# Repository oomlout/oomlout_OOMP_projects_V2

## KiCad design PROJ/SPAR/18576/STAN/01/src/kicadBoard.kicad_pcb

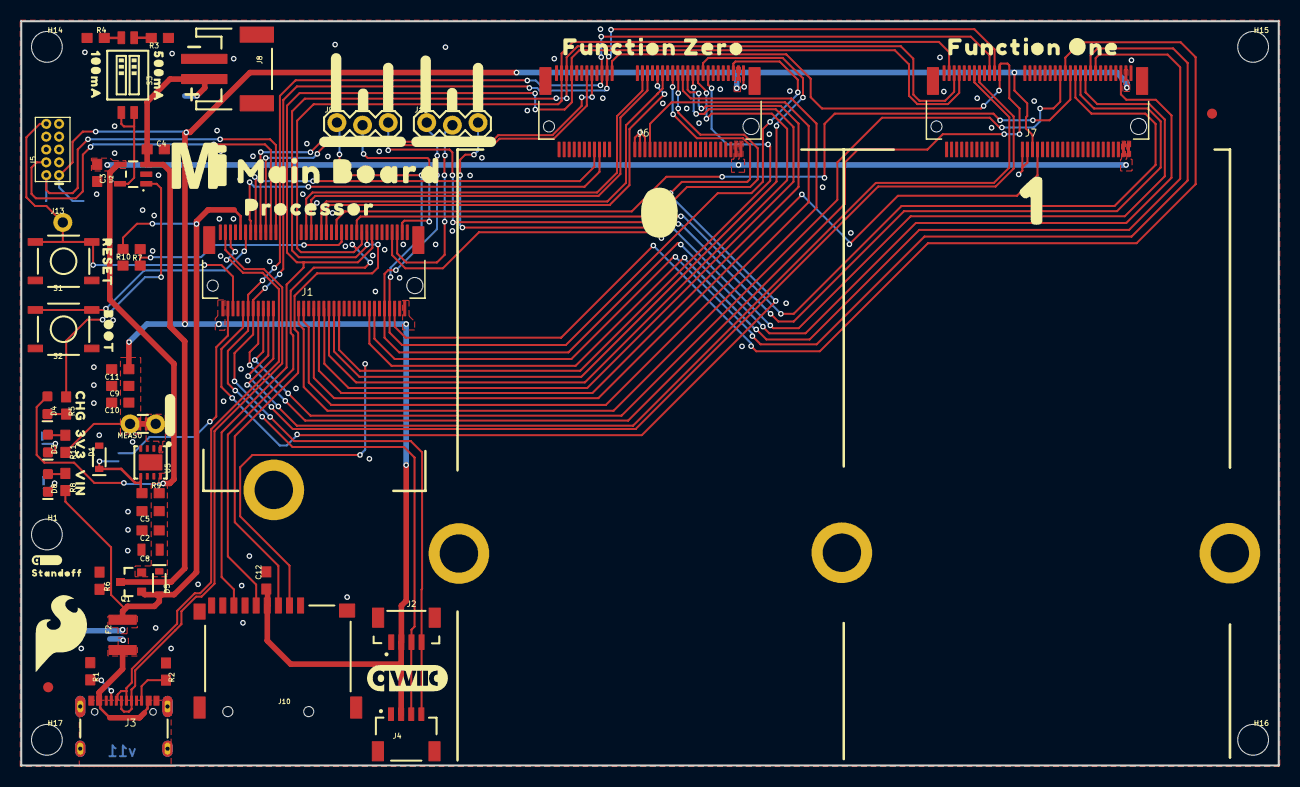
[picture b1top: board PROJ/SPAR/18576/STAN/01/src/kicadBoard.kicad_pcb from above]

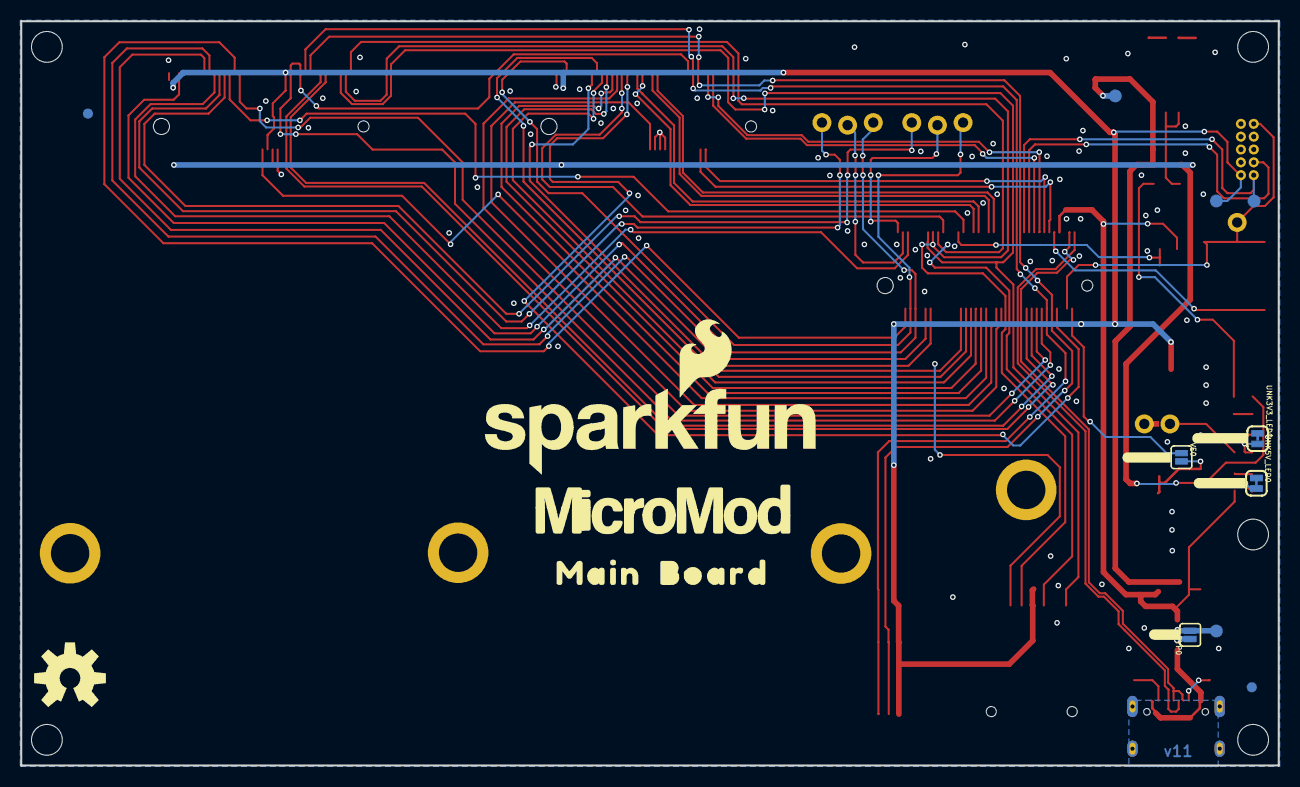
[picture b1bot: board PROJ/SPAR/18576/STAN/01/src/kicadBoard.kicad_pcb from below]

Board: 2 copper layers, 124.5 x 73.7 mm, 104 parts (19 on the bottom side), 65 nets.

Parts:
BYP0: JUMPER-SMT_2_NO_SILK; SMT-JUMPER_2_NO_SILK
C2, C11: 0.22uF; 0603
C3, C4: 4.7uF; 0603
C5, C10, C12: 0.1uF; 0603
C8: 10uF; 0805
C9: 1.0uF; 0603
D1: 3.3V; SOD-323
D3, D8: RED; LED-0603
D4: Yellow; LED-0603
D5: 1A/23V/620mV; SOD-323
F2: 6V/2A; 1210
FD1, FD2, FD3, FD4: FIDUCIAL1X2; FIDUCIAL-1X2
FRAME1: FRAME-LEDGER; CREATIVE_COMMONS
FRAME2: FRAME-LEDGERNO_FOOTPRINT; DUMMY
H1, H14, H15, H16, H17: STAND-OFFTIGHT; STAND-OFF-TIGHT
H2, H3, H4, H8: STAND-OFF-REFLOW-M2.5_2.5MM_TALL; STAND-OFF-REFLOW-M2.5
J1: MICROMOD-2222-C; M.2-CONNECTOR-E
J2: Vertical Qwiic Connector; JST04_1MM_VERT
J3: USB-C-16P-2LAYER-PADS
J4: QWIIC_RIGHT_ANGLE; JST04_1MM_RA
J5: CORTEX_JTAG_DEBUG_MINIMUM_PTH; 2X5-PTH-1.27MM
J6, J7: MICROMOD_FUNCTION_MAIN; M.2-CONNECTOR-E-FUNCTION-STANDARD
J8: JST-2-SMD
J9, J11: 1X03_LOCK
J10: MICRO-SD-PUSH-PUSH-EXT-PIN; MICROSD-EXTERNALPIN
J13: 1X01_NO_SILK
LOGO1: QWIIC_LOGO_8MM; QWIIC_8MM
LOGO2: SFE_LOGO_NAME_FLAME.3_INCH; SFE_LOGO_NAME_FLAME_.3
LOGO3: OSHW-LOGOL; OSHW-LOGO-L
MEAS0: JUMPER-COMBO_2_NC_TRACE; COMBO-JUMPER_2_NC_TRACE
Q1: 3.1A/30V/105mΩ; SOT23-3
R1, R2: 5.1k; 0603
R3: 2.0k; 0603
R4, R6, R7: 10k; 0603
R5, R11: 1k; 0603
R8: 4.7k; 0603
R9: 100k; 0603
R10: 20k; 0603
S1: Reset; TACTILE_SWITCH_SMD_5.2MM
S2: BOOT; TACTILE_SWITCH_SMD_5.2MM
S3: DIP-02-SMD-50MIL; DIPSWITCH-02-50MIL
TP1, TP2, TP3, TP4: TEST-POINT3X5; PAD.03X.05
U2: MCP73831; SOT23-5
U5: AP7361C-33; UDFN-8
U$1: #3V3_EN#18
U$2: #3V3_LED#17
U$3: #VIN_LED#16
U$4: 3V332533
U$5: VIN32532
U$6: CHG32531
U$7: #PTC#18
U$8: BOOT32541
U$9: RESET32540
U$10: PROCESSOR525
U$11: FUNCTION_ZERO520
U$12: FUNCTION_ONE524
U$13: MAIN523
U$14: MICROMOD_MI_LOGO_1
U$15: 0523
U$16: 1524
U$17: MICROMOD_LOGO_1
U$18: BOARD524
U$19: 100MA6
U$20: 500MA101
U$21: MAIN_BOARD5523
U$22: QWIIC_3MM
U$23: STANDOFF501
U$24: SFE_LOGO_FLAME_.3
U$25: #ALT_PWR_EN0#510
U$26: #ALT_PWR_EN1#510
U$27: #FC1#G3#518
U$28: #FC1#G4#518
U$29: #G6#517
U$30: #PWR_EN0#517
U$31: #PWR_EN1#517
U$32: #G5#517
U$33: #MEAS#40313513
UNK3V3_LED0, UNK5V_LED0: JUMPER-SMT_2_NC_TRACE_SILK; SMT-JUMPER_2_NC_TRACE_SILK
VE0: JUMPER-SMT_2_NO_SILK; SMT-JUMPER_2_NO_SILK

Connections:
3.3V: C9.1, C10.1, C11.1, C12.1, J1.2, J1.74, J2.2, J4.2, J5.1, J6.73, J7.36, J7.73, J10.4, MEAS0.2, MEAS0.4, R11.2, TP2.1
3.3V_EN: J1.4, VE0.1
3.3V_EN_VE: D1.C, R9.1, U5.5, VE0.2
A0-PROCESSOR: J1.34, J6.38
A1-PROCESSOR: J1.38, J7.38
CTS1-PROCESSOR: J1.15, J6.16
D0-PROCESSOR: J1.10, J6.47
D1-PROCESSOR: J1.18, J7.47
D+: J1.3, J3.A6, J3.B6
D-: J1.5, J3.A7, J3.B7
G0-PROCESSOR: J1.40, J6.53
G1-PROCESSOR: J1.42, J6.55
G2-PROCESSOR: J1.44, J6.57
G3-PROCESSOR: J1.46, J6.59
G4-PROCESSOR/SD_CARD_~CS: J1.48, J6.61, J10.2
G5-JUMPER: J1.71, J11.2
G5-PROCESSOR: J7.53, J9.3
G6-PROCESSOR: J7.55, J11.3
G7-PROCESSOR: J1.69, J7.57
G8-PROCESSOR: J1.62, J7.59
G9-PROCESSOR: J1.60, J7.61
GND: C2.2, C3.2, C4.2, C5.2, C8.2, C9.2, C10.2, C11.2, C12.2, D1.A, H2.1, H3.1, H4.1, H8.1, J1.1, J1.7, J1.33, J1.36, J1.39, J1.45, J1.75, J2.1, J3.GND, J3.GND2, J4.1, J5.3, J5.5, J5.9, J6.1, J6.32, J6.33, J6.34, J6.36, J6.39, J6.45, J6.75, J7.1, J7.32, J7.33, J7.34, J7.39, J7.45, J7.75, J8.1, J10.6, J10.10, J10.11, J10.12, J10.13, R1.1, R2.1, R3.1, R4.1, R6.1, R7.1, S1.1, S1.2, S2.1, S2.2, U2.2, U5.4, U5.EP, UNK3V3_LED0.1, UNK5V_LED0.1
HOST_D+: J1.35, J6.35
HOST_D-: J1.37, J6.37
I2C_SCL: J1.14, J2.4, J4.4, J6.21, J7.21
I2C_SDA: J1.12, J2.3, J4.3, J6.19, J7.19
I2C_~INT: J1.16, J6.23, J7.23
unnamed: MEAS0.1, MEAS0.3, U5.1
unnamed: D8.C, UNK5V_LED0.2
unnamed: D3.A, R11.1
unnamed: J3.B5, R2.2
unnamed: J3.A5, R1.2
unnamed: R3.2, S3.1
unnamed: BYP0.1, F2.1, J3.VBUS1, J3.VBUS2
unnamed: R4.2, S3.2
unnamed: J1.73, J9.2
unnamed: D3.C, UNK3V3_LED0.2
unnamed: D8.A, R8.1
unnamed: D4.C, R5.2
unnamed: R5.1, U2.1
PROCESSOR_CAN-RX: J1.41, J6.43
PROCESSOR_CAN-TX: J1.43, J6.41
PWM0-PROCESSOR: J1.32, J6.51
PWM1-PROCESSOR: J1.47, J7.51
PWR_EN0: J1.68, J6.71, J9.1
PWR_EN1: J1.66, J7.71, J11.1
RTS1-PROCESSOR: J1.13, J6.18
RX1-PROCESSOR: J1.19, J6.13
RX2-PROCESSOR: J1.20, J7.13
SHLD: S3.3, S3.4, U2.5
SPI_PROCESSOR_SCK: J1.57, J6.3, J7.3, J10.5
SPI_PROCESSOR_SDI: J1.61, J6.7, J7.7, J10.7
SPI_PROCESSOR_SDO: J1.59, J6.5, J7.5, J10.3
SWDCK: J1.21, J5.4
SWDIO: J1.23, J5.2, TP1.1
TX1-PROCESSOR: J1.17, J6.15
TX2-PROCESSOR: J1.22, J7.15
VCC: C2.1, C3.1, C5.1, C8.1, D4.A, D5.C, J6.72, J6.74, J7.72, J7.74, Q1.2, R9.2, U2.4, U5.8
VIN: BYP0.2, D5.A, F2.2, J1.9, Q1.1, R6.2, R8.2, R10.2, TP4.1
VIN/3: J1.49, R7.2, R10.1
V_BATT: C4.1, J8.2, Q1.3, TP3.1, U2.3
~BOOT: J1.11, S2.3, S2.4
~CS0-PROCESSOR: J1.55, J6.49
~CS1-PROCESSOR: J1.70, J7.49
~RESET: J1.6, J5.10, J13.1, S1.3, S1.4

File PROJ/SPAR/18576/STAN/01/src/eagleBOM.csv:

"Part";"Value";"Device";"Package";"Description";"DESIGNER";"PROD_ID";"REV";"SF_ID";"VALUE";
"3V3_LED";"JUMPER-SMT_2_NC_TRACE_SILK";"JUMPER-SMT_2_NC_TRACE_SILK";"SMT-JUMPER_2_NC_TRACE_SILK";"Normally closed trace jumper";"";"";"";"";"";
"5V_LED";"JUMPER-SMT_2_NC_TRACE_SILK";"JUMPER-SMT_2_NC_TRACE_SILK";"SMT-JUMPER_2_NC_TRACE_SILK";"Normally closed trace jumper";"";"";"";"";"";
"BYP";"JUMPER-SMT_2_NO_SILK";"JUMPER-SMT_2_NO_SILK";"SMT-JUMPER_2_NO_SILK";"Normally open jumper";"";"";"";"";"";
"C2";"0.22uF";"0.22UF-0603-25V-10%";"0603";"0.22µF ceramic capacitors";"";"CAP-07822";"";"";"0.22uF";
"C3";"4.7uF";"4.7UF-0603-6.3V-(10%)";"0603";"4.7µF ceramic capacitors";"";"CAP-08280";"";"";"4.7uF";
"C4";"4.7uF";"4.7UF-0603-35V-(20%)";"0603";"4.7µF ceramic capacitors";"";"CAP-14106";"";"";"4.7uF";
"C5";"0.1uF";"0.1UF-0603-25V-(+80/-20%)";"0603";"0.1µF ceramic capacitors";"";"CAP-00810";"";"";"0.1uF";
"C8";"10uF";"10UF-0805-10V-10%";"0805";"10.0µF ceramic capacitors";"";"CAP-11330";"";"";"10uF";
"C9";"1.0uF";"1.0UF-0603-16V-10%";"0603";"1µF ceramic capacitors";"";"CAP-00868";"";"";"1.0uF";
"C10";"0.1uF";"0.1UF-0603-25V-(+80/-20%)";"0603";"0.1µF ceramic capacitors";"";"CAP-00810";"";"";"0.1uF";
"C11";"0.22uF";"0.22UF-0603-25V-10%";"0603";"0.22µF ceramic capacitors";"";"CAP-07822";"";"";"0.22uF";
"C12";"0.1uF";"0.1UF-0603-25V-(+80/-20%)";"0603";"0.1µF ceramic capacitors";"";"CAP-00810";"";"";"0.1uF";
"D1";"3.3V";"DIODE-ZENER-MM3Z3V3T1G";"SOD-323";"Zener Diode";"";"DIO-11284";"";"";"3.3V";
"D3";"RED";"LED-RED0603";"LED-0603";"Red SMD LED";"";"DIO-00819";"";"";"RED";
"D4";"Yellow";"LED-YELLOW0603";"LED-0603";"Yellow SMD LED";"";"DIO-09003";"";"";"Yellow";
"D5";"1A/23V/620mV";"DIODE-SCHOTTKY-BAT20J";"SOD-323";"Schottky diode";"";"DIO-11623";"";"";"1A/23V/620mV";
"D8";"RED";"LED-RED0603";"LED-0603";"Red SMD LED";"";"DIO-00819";"";"";"RED";
"F2";"6V/2A";"PPTC_6V2A";"1210";"Resettable Fuse PPTC";"";"RES-14313";"";"";"6V/2A";
"FD1";"FIDUCIAL1X2";"FIDUCIAL1X2";"FIDUCIAL-1X2";"Fiducial Alignment Points";"";"";"";"";"";
"FD2";"FIDUCIAL1X2";"FIDUCIAL1X2";"FIDUCIAL-1X2";"Fiducial Alignment Points";"";"";"";"";"";
"FD3";"FIDUCIAL1X2";"FIDUCIAL1X2";"FIDUCIAL-1X2";"Fiducial Alignment Points";"";"";"";"";"";
"FD4";"FIDUCIAL1X2";"FIDUCIAL1X2";"FIDUCIAL-1X2";"Fiducial Alignment Points";"";"";"";"";"";
"FRAME1";"FRAME-LEDGER";"FRAME-LEDGER";"CREATIVE_COMMONS";"Schematic Frame - Ledger";"";"";"";"";"";
"H2";"STAND-OFF-REFLOW-M2.5_2.5MM_TALL";"STAND-OFF-REFLOW-M2.5_2.5MM_TALL";"STAND-OFF-REFLOW-M2.5";"Stand Off Reflow Compatible";"";"HW-14899";"";"";"";
"H3";"STAND-OFF-REFLOW-M2.5_2.5MM_TALL";"STAND-OFF-REFLOW-M2.5_2.5MM_TALL";"STAND-OFF-REFLOW-M2.5";"Stand Off Reflow Compatible";"";"HW-14899";"";"";"";
"H4";"STAND-OFF-REFLOW-M2.5_2.5MM_TALL";"STAND-OFF-REFLOW-M2.5_2.5MM_TALL";"STAND-OFF-REFLOW-M2.5";"Stand Off Reflow Compatible";"";"HW-14899";"";"";"";
"H8";"STAND-OFF-REFLOW-M2.5_2.5MM_TALL";"STAND-OFF-REFLOW-M2.5_2.5MM_TALL";"STAND-OFF-REFLOW-M2.5";"Stand Off Reflow Compatible";"";"HW-14899";"";"";"";
"H14";"STAND-OFFTIGHT";"STAND-OFFTIGHT";"STAND-OFF-TIGHT";"Stand Off";"";"";"";"";"";
"H15";"STAND-OFFTIGHT";"STAND-OFFTIGHT";"STAND-OFF-TIGHT";"Stand Off";"";"";"";"";"";
"H16";"STAND-OFFTIGHT";"STAND-OFFTIGHT";"STAND-OFF-TIGHT";"Stand Off";"";"";"";"";"";
"H17";"STAND-OFFTIGHT";"STAND-OFFTIGHT";"STAND-OFF-TIGHT";"Stand Off";"";"";"";"";"";
"J1";"MICROMOD-2222-C";"MICROMOD-2222-C";"M.2-CONNECTOR-E";"MicroMod Connector";"";"CONN-14877";"";"";"";
"J2";"Vertical Qwiic Connector";"QWIIC_CONNECTOR";"JST04_1MM_VERT";"SparkFun I2C Standard Qwiic Connector";"";"CONN-14483";"";"";"Vertical Qwiic Connector";
"J3";"";"USB_C_2-LAYER_PADS";"USB-C-16P-2LAYER-PADS";"USB Type C 16Pin Connector";"";"CONN-14122";"";"";"";
"J4";"QWIIC_RIGHT_ANGLE";"QWIIC_CONNECTORJS-1MM";"JST04_1MM_RA";"SparkFun I2C Standard Qwiic Connector";"";"CONN-13694";"";"";"QWIIC_RIGHT_ANGLE";
"J5";"CORTEX_JTAG_DEBUG_MINIMUM_PTH";"CORTEX_JTAG_DEBUG_MINIMUM_PTH";"2X5-PTH-1.27MM";"Cortex Debug Connector - 10 pin";"";"";"";"";"";
"J6";"MICROMOD_FUNCTION_MAIN";"MICROMOD_FUNCTION_MAIN";"M.2-CONNECTOR-E-FUNCTION-STANDARD";"MicroMod Connector";"";"CONN-14877";"";"";"";
"J7";"MICROMOD_FUNCTION_MAIN";"MICROMOD_FUNCTION_MAIN";"M.2-CONNECTOR-E-FUNCTION-STANDARD";"MicroMod Connector";"";"CONN-14877";"";"";"";
"J8";"";"JST_2MM_MALE";"JST-2-SMD";"JST 2MM MALE RA CONNECTOR";"";"CONN-11443";"";"PRT-08612";"";
"J9";"";"CONN_03LOCK";"1X03_LOCK";"Multi connection point. Often used as Generic Header-pin footprint for 0.1 inch spaced/style header connections";"";"";"";"";"";
"J10";"MICRO-SD-PUSH-PUSH-EXT-PIN";"MICRO-SD-PUSH-PUSH-EXT-PIN";"MICROSD-EXTERNALPIN";"microSD Socket for Transflash";"";"CONN-16110";"";"";"";
"J11";"";"CONN_03LOCK";"1X03_LOCK";"Multi connection point. Often used as Generic Header-pin footprint for 0.1 inch spaced/style header connections";"";"";"";"";"";
"J13";"";"CONN_01PTH_NO_SILK_YES_STOP";"1X01_NO_SILK";"Single connection point. Often used as Generic Header-pin footprint for 0.1 inch spaced/style header connections";"";"";"";"";"";
"LOGO1";"QWIIC_LOGO_8MM";"QWIIC_LOGO_8MM";"QWIIC_8MM";"Qwiic Logos for placement on schematic and PCB. The 5.5mm silk logo is best for placing next to Qwiic connector.";"";"";"";"";"";
"LOGO2";"SFE_LOGO_NAME_FLAME.3_INCH";"SFE_LOGO_NAME_FLAME.3_INCH";"SFE_LOGO_NAME_FLAME_.3";"SparkFun Font Logo w/ Flame";"";"";"";"";"";
"LOGO3";"OSHW-LOGOL";"OSHW-LOGOL";"OSHW-LOGO-L";"Open-Source Hardware (OSHW) Logo";"";"";"";"";"";
"MEAS";"JUMPER-COMBO_2_NC_TRACE";"JUMPER-COMBO_2_NC_TRACE";"COMBO-JUMPER_2_NC_TRACE";"";"";"";"";"";"";
"Q1";"3.1A/30V/105mΩ";"MOSFET_PCH-DMG2307L";"SOT23-3";"P-channel MOSFETs";"";"TRANS-11308";"";"";"3.1A/30V/105mΩ";
"R1";"5.1k";"5.1KOHM5.1KOHM-0603-1/10W-1%";"0603";"";"";"RES-12083";"";"";"5.1k";
"R2";"5.1k";"5.1KOHM5.1KOHM-0603-1/10W-1%";"0603";"";"";"RES-12083";"";"";"5.1k";
"R3";"2.0k";"2.0KOHM-0603-1/10W-5%";"0603";"2kΩ resistor";"";"RES-08296";"";"";"2.0k";
"R4";"10k";"10KOHM-0603-1/10W-1%";"0603";"10kΩ resistor";"";"RES-00824";"";"";"10k";
"R5";"1k";"1KOHM-0603-1/10W-1%";"0603";"1kΩ resistor";"";"RES-07856";"";"";"1k";
"R6";"10k";"10KOHM-0603-1/10W-1%";"0603";"10kΩ resistor";"";"RES-00824";"";"";"10k";
"R7";"10k";"10KOHM-0603-1/10W-1%";"0603";"10kΩ resistor";"";"RES-00824";"";"";"10k";
"R8";"4.7k";"4.7KOHM-0603-1/10W-1%";"0603";"4.7kΩ resistor";"";"RES-07857";"";"";"4.7k";
"R9";"100k";"100KOHM-0603-1/10W-1%";"0603";"100kΩ resistor";"";"RES-07828";"";"";"100k";
"R10";"20k";"20KOHM-0603-1/10W-1%";"0603";"20kΩ resistor";"";"RES-09383";"";"";"20k";
"R11";"1k";"1KOHM-0603-1/10W-1%";"0603";"1kΩ resistor";"";"RES-07856";"";"";"1k";
"S1";"Reset";"MOMENTARY-SWITCH-SPST-SMD-5.2-TALL-REDUNDANT";"TACTILE_SWITCH_SMD_5.2MM";"Momentary Switch (Pushbutton) - SPST";"";"SWCH-14139";"";"";"";
"S2";"BOOT";"MOMENTARY-SWITCH-SPST-SMD-5.2-TALL-REDUNDANT";"TACTILE_SWITCH_SMD_5.2MM";"Momentary Switch (Pushbutton) - SPST";"";"SWCH-14139";"";"";"";
"S3";"DIP-02-SMD-50MIL";"DIP-02-SMD-50MIL";"DIPSWITCH-02-50MIL";"2-Position DIP Switch";"";"SWCH-13215";"";"";"";
"TP1";"TEST-POINT3X5";"TEST-POINT3X5";"PAD.03X.05";"SparkFun Test Points";"";"";"";"";"";
"TP2";"TEST-POINT3X5";"TEST-POINT3X5";"PAD.03X.05";"SparkFun Test Points";"";"";"";"";"";
"TP3";"TEST-POINT3X5";"TEST-POINT3X5";"PAD.03X.05";"SparkFun Test Points";"";"";"";"";"";
"TP4";"TEST-POINT3X5";"TEST-POINT3X5";"PAD.03X.05";"SparkFun Test Points";"";"";"";"";"";
"U2";"MCP73831";"MCP73831";"SOT23-5";"MCP73831T Li-Ion, Li-Pol Controller";"";"IC-09995";"";"";"";
"U5";"AP7361C-33";"AP7361C-33FGEUDFN-8";"UDFN-8";"AP7361C 3.3V LDO Regulator";"";"VREG-14094";"";"";"";
"VE";"JUMPER-SMT_2_NO_SILK";"JUMPER-SMT_2_NO_SILK";"SMT-JUMPER_2_NO_SILK";"Normally open jumper";"";"";"";"";"";

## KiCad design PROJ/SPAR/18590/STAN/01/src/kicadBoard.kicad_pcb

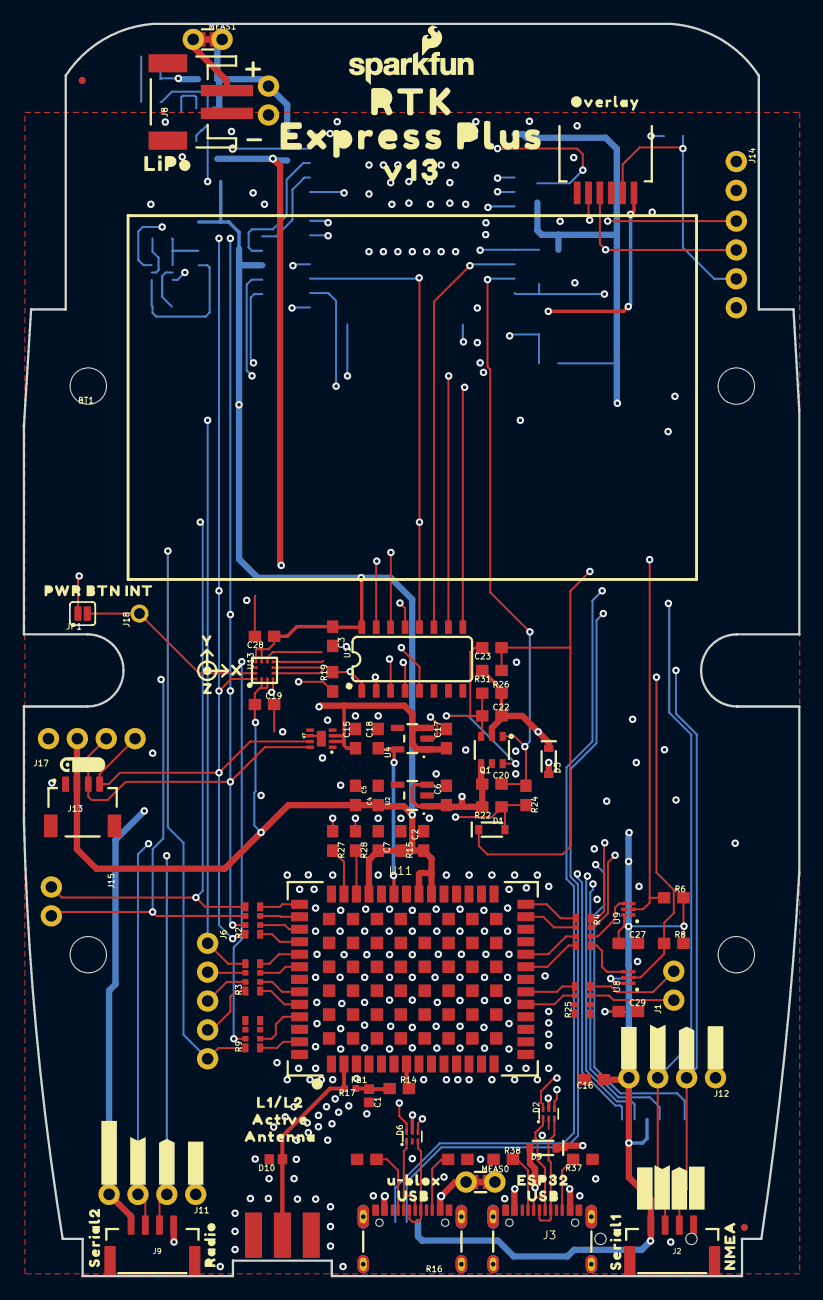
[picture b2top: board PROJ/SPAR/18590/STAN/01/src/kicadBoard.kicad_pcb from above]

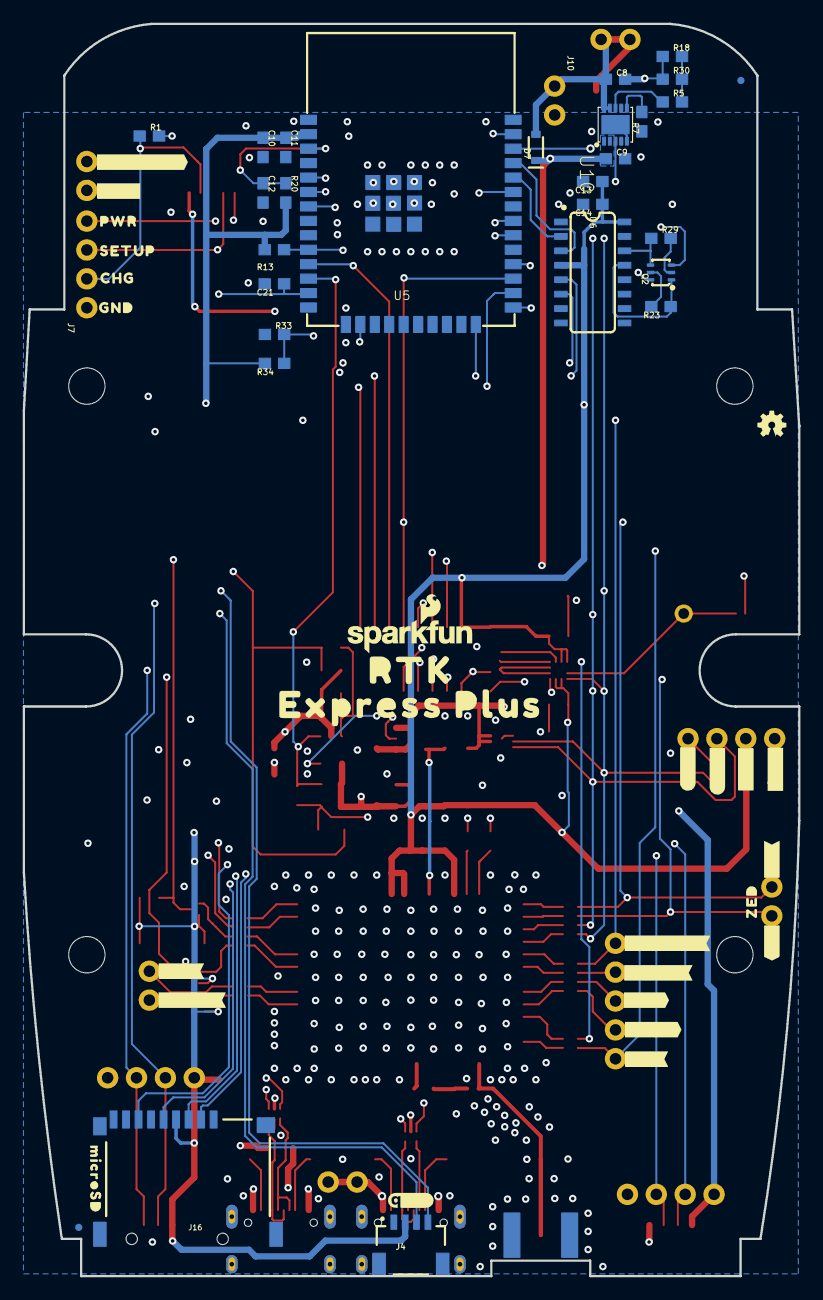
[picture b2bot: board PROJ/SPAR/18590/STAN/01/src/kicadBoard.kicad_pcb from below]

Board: 4 copper layers, 68.2 x 110.1 mm, 171 parts (56 on the bottom side), 92 nets.

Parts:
BT1: LIPO-OUTLINE1000; LIPO-1000
C1: 47pF; 0402
C2, C4, C6, C17, C18: 1.0uF; 0603
C3, C5, C7, C11, C12, C13, C15, C16, C21, C22, C23, C27, C28, C29: 0.1uF; 0603
C8, C9: 4.7uF; 0603
C10, C14, C19, C20: 10uF; 0603
D1: 250mA/100V; SOD-323
D2, D6: PRTR5V0U2F; SOT886
D3, D7, D9: 3A/10V/280mV; SOD-323
D10: PESD0402-0402; 0402
E1: SMA; SMA-EDGE
FB1: 2.66Ω; 0402-TIGHT
FRAME2: FRAME-LEDGER; CREATIVE_COMMONS
FRAME3: FRAME-LEDGERNO_FOOTPRINT; DUMMY
J1, J10, J14, J15: 1X02_NO_SILK
J2, J9: JST-4-SMD-1.25MM-LOCKING
J3, J5: USB Female Type C Connector; USB-C-16P_4LAYER-PADS
J4: Qwiic Right Angle; JST04_1MM_RA
J6: 1X05_NO_SILK
J7, J11, J12: 1X04_NO_SILK
J8: JST-2-SMD
J13: Internal; JST04_1MM_RA
J16: MICRO-SD-PUSH-PUSH-EXT-PIN; MICROSD-EXTERNALPIN
J17: Qwiic Right Angle; 1X04_NO_SILK
J18: 1X01_NO_SILK
J19: FPC_6_1MM-LIF
JP1: JUMPER-SMT_2_NO_SILK; SMT-JUMPER_2_NO_SILK
JP21, JP61, JP71, JP81: FIDUCIALUFIDUCIAL; FIDUCIAL-MICRO
LOGO1: OSHW-LOGOMINI; OSHW-LOGO-MINI
LOGO2, LOGO3: SFE_LOGO_NAME_FLAME.1_INCH; SFE_LOGO_NAME_FLAME_.1
MEAS0, MEAS1: JUMPER-COMBO_2_NC_TRACE; COMBO-JUMPER_2_NC_TRACE
Q1: SIL2308-TP; SOT26
Q2: MBT3904DW1T1; SC70-6
R1: 470; 0603
R2, R3, R4, R9, R25: 33; 1206_RA
R5: 0; 0603
R6, R8, R18, R23, R29, R31, R33: 10k; 0603
R7, R19: 1k; 0603
R13, R15, R20, R22, R26: 100k; 0603
R14: 10; 0603
R16, R17, R37, R38: 5.1k; 0603
R24: 300k; 0603
R27, R28: 27; 0603
R30: 150k; 0603
R34: 3.3k; 0603
U1: 74HC4052D; SO16
U2: AP2112K-3.3; SOT23-5
U4: STLQ015-3.3V; SOT23-5
U5: ESP-WROOM-3232D; ESP-WROOM-32D
U6: CH340C; SO016
U7: MAX17048; DFN-8
U8, U9: NC7SZ14-D; SIP6
U10: MCP73833; DFN-10
U11: U-BLOX_ZED_F9R; UBLOX_ZED_F9R
U13: LIS2DH12; LGA-12-LISDH12
U$1: V130
U$2: SPECIAL_INSTRUCTIONS-ORDERING; ORDERING_INSTRUCTIONS
U$3: #TX_RDY#0
U$4: INT0
U$5, U$47: #3V3#0
U$6: L1#L20
U$7, U$74: RTK0
U$8: OVERLAY0
U$9: PWR_BTN1
U$10: #RTK#1
U$11: #PPS#0
U$12, U$22: EXPRESS_PLUS0
U$13: ACTIVE1
U$14: #RX#2
U$15: ANTENNA2
U$16: ZED0
U$17: ##SAFE##5
U$23: #3#5#5V#0
U$24: X0
U$26: 1553DBK-ENCLOSURE
U$27: LIPO0
U$28: ##RST##4
U$29: SERIAL10
U$30, U$93: QWIIC_4MM
U$32: #FENCE#3
U$33: CHG2
U$34: GND3
U$35: U#BLOX0
U$36, U$66: USB1
U$38, U$48, U$82: #GND#0
U$39: #RX2#2
U$40: #TX2#1
U$41: PWR0
U$42: SETUP1
U$43: SERIAL20
U$45, U$68: #RX1#2
U$46, U$65: #TX1#1
U$49: NMEA1
U$50: RADIO0
U$55: Y1
U$56: Z2
U$60: #ESP_RST#0
U$67: ESP320
U$70: #GND#2
U$72: #TX#1
U$83: MICROSD0
U$84: #GND#1
U$85: #3V3#2
U$86: #SCL#1
U$87: #SDA#0
U$88: #D_SEL#0

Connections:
3.3V: C2.1, C3.1, C4.1, C5.2, C7.2, C10.1, C11.1, C13.1, C14.1, C16.1, C19.1, C27.1, C28.1, C29.1, J2.1, J4.2, J12.4, J13.2, J16.4, J17.2, R6.2, R8.2, R13.2, R15.2, R20.2, R34.2, U1.16, U2.5, U5.2, U6.4, U6.16, U8.P6, U9.P6, U11.P33, U11.P34, U11.P38, U13.2, U13.3, U13.9, U13.10
ANT_VCC: C1.1, FB1.2, R14.1
CC1: J5.A5, R17.2
CC2: J5.B5, R16.2
CC3: J3.B5, R37.2
CC4: J3.A5, R38.2
CHG_LED: R1.2, U10.3
CHG_LED_RES: J7.2, J19.2, R1.1
CHG_THERM1: R5.2, R18.2, R30.2
D+: D6.4, R27.1
D+1: D2.4, U6.5
D-: D6.6, R28.1
D-1: D2.6, U6.6
ESP32_EN: C12.1, J14.1, Q2.3, R20.1, U5.3
ESP32_RXI: U5.34, U6.2
ESP32_TXO: U5.35, U6.3
ESP32_~DTR: Q2.1, R23.1, U6.13
ESP32_~RTS: Q2.4, R29.1, U6.14
ESP_0/BOOT: Q2.6, U5.25
ESP_2/MUX_A: U1.10, U5.24
ESP_4/ACCEL_INT: J18.1, JP1.1, U13.12
ESP_4/MUX_B: U1.9, U5.26
ESP_13/POWER_CTRL: D1.A, R22.1, R24.2, U5.16
ESP_14/SETUP_BUTTON: C21.1, J7.3, J19.4, U5.13
ESP_18/SCK: J16.5, U5.30
ESP_19/POCI: J16.7, U5.31
ESP_21/SDA: J4.3, J13.3, J17.3, R2.P7, U5.33, U7.8, U13.4
ESP_22/SCL: J4.4, J13.4, J17.4, R2.P8, U5.36, U7.7, U13.1
ESP_23/PICO: J16.3, U5.37
ESP_25/SD_~CS: J16.2, R13.1, U5.10
ESP_26/DAC2: U1.11, U5.11
ESP_26/ZED_TX_READY_LV: R3.P4, U11.P46
ESP_27/FAST_OFF: C20.2, Q1.G1, R24.1, U5.12
ESP_D1+: D2.3, J3.A6, J3.B6
ESP_D1-: D2.1, J3.A7, J3.B7
ESP_I16/ZED-TXO1: J15.1, R2.P5, U1.12, U5.27
ESP_I34/ZED_TX_READY: J6.1, R3.P5, U5.6
ESP_I35/DEVICE_SENSE: R33.2, R34.1, U5.7
ESP_I39/ADC39: U1.4, U5.5
ESP_O17/ZED-RXI1: J15.2, R2.P6, R19.2, U1.1
EXTERNAL_DATA_IN: J2.3, J12.2, U1.3
EXTERNAL_DATA_OUT: J2.2, J12.3, U1.13
EXTINT_LV: R9.P2, U11.P51
EXT_DIR: R6.1, U1.15, U9.P2
EXT_WT: R8.1, U1.2, U8.P2
FENCE_LV: R25.P6, U11.P19
GND: C1.2, C2.2, C3.2, C4.2, C5.1, C6.2, C7.1, C8.2, C9.2, C10.2, C11.2, C12.2, C13.2, C14.2, C15.2, C16.2, C17.2, C18.2, C19.2, C21.2, C27.2, C28.2, C29.2, D2.2, D6.2, D10.2, E1.GND@0, E1.GND@1, E1.GND@2, E1.GND@3, J2.4, J3.GND, J3.GND2, J3.SHLD1, J3.SHLD2, J3.SHLD3, J3.SHLD4, J4.1, J5.GND, J5.GND2, J5.SHLD1, J5.SHLD2, J5.SHLD3, J5.SHLD4, J7.1, J8.1, J9.4, J10.2, J11.1, J12.1, J13.1, J14.2, J16.6, J16.10, J16.11, J16.12, J16.13, J17.1, J19.6, Q1.S1, R7.1, R15.1, R16.1, R17.1, R18.1, R30.1, R33.1, R37.1, R38.1, U1.6, U1.7, U1.8, U2.2, U4.2, U5.1, U5.15, U5.38, U5.GND, U5.GNDT1, U5.GNDT2, U5.GNDT3, U5.GNDT4, U5.GNDT5, U5.GNDT6, U5.GNDT7, U5.GNDT8, U6.1, U7.1, U7.4, U7.6, U7.9, U8.P3, U9.P3, U10.5, U10.11, U11.G1, U11.G2, U11.G3, U11.G4, U11.G5, U11.G6, U11.G7, U11.G8, U11.G9, U11.G10, U11.G11, U11.G12, U11.G13, U11.G14, U11.G15, U11.G16, U11.G17, U11.G18, U11.G19, U11.G20, U11.G21, U11.G22, U11.G23, U11.G24, U11.G25, U11.G26, U11.G27, U11.G28, U11.G29, U11.G30, U11.G31, U11.G32, U11.G33, U11.G34, U11.G35, U11.G36, U11.G37, U11.G38, U11.G39, U11.G40, U11.G41, U11.G42, U11.G43, U11.G44, U11.G45, U11.G46, U11.G47, U11.G48, U11.P1, U11.P3, U11.P12, U11.P14, U11.P32, U11.P37, U11.P41, U11.P48, U13.5, U13.6, U13.7, U13.8
GPS_ANT1: D10.1, E1.SIG, FB1.1, U11.P2
LIPO_RAW: J8.2, MEAS1.1, MEAS1.3
unnamed: R4.P4, U11.P22
unnamed: R4.P3, U11.P23
unnamed: J5.VBUS1, J5.VBUS2, MEAS0.1, MEAS0.3
unnamed: R5.1, U10.8
unnamed: R19.1, U5.28
unnamed: R27.2, U11.P40
unnamed: R28.2, U11.P39
unnamed: R14.2, U11.P7
unnamed: C22.1, C23.2, Q1.D1, Q1.G2, R26.1
unnamed: Q2.5, R23.2
unnamed: Q2.2, R29.2
unnamed: D9.A, J3.VBUS1, J3.VBUS2
POWER_BTN: C23.1, D1.C, J7.4, J19.5, JP1.2, R31.1
PPS_LV: R9.P1, U11.P53
PROG1: R7.2, U10.6
RTK_STAT_LV: R25.P5, U11.P20
RX2_LV: R4.P2, U11.P26
RXLV: R2.P3, U11.P43
SCL_LV: R2.P1, U11.P45
SDA_LV: R2.P2, U11.P44
TX2_LV: R4.P1, U11.P27
TXLV: R2.P4, U11.P42
UNP_D+: D6.3, J5.A6, J5.B6
UNP_D-: D6.1, J5.A7, J5.B7
VOUT: C6.1, C20.1, J9.1, J11.4, Q1.D2, R22.2, U2.1, U2.3
V_BATT: C8.1, C15.1, C17.1, D7.A, J10.1, MEAS1.2, MEAS1.4, U4.1, U4.3, U7.2, U7.3, U10.9, U10.10
V_BKCP: C18.1, U4.5, U11.P36
V_RAW: C9.1, C22.2, D3.C, D7.C, Q1.S2, R26.2, R31.2, U10.1, U10.2
V_USB: D2.5, D3.A, D6.5, D9.C, J19.1, MEAS0.2, MEAS0.4
ZED-RXI2: J9.3, J11.2, R4.P7
ZED-TXO2: J9.2, J11.3, R4.P8
ZED_DIR: R4.P6, U9.P4
ZED_D_SEL: J6.2, R3.P6
ZED_D_SEL_LV: R3.P3, U11.P47
ZED_EXTINT: R9.P7, U1.5
ZED_FENCE_STAT: J1.1, R25.P3
ZED_PPS_STAT: J6.5, R9.P8, U1.14
ZED_RTK_STAT: J1.2, R25.P4
ZED_WT: R4.P5, U8.P4
ZED_~RESET: J6.3, R3.P7
ZED_~RESET_LV: R3.P2, U11.P49
ZED_~SAFE: J6.4, R3.P8
ZED_~SAFE_LV: R3.P1, U11.P50

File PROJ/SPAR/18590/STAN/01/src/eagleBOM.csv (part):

"Part";"Value";"Device";"Package";"Description";"DESIGNER";"DIGIKEY";"DIGIKEY_PART";"MOUSE_PART";"PROD_ID";"REV";"SF_ID";"SF_SKU";"VALUE";
"BT1";"LIPO-OUTLINE1000";"LIPO-OUTLINE1000";"LIPO-1000";"LiPo Battery Outlines";"";"";"";"";"BATT-13243";"";"";"PRT-13813";"";
"C1";"47pF";"47PF-0402-25V-5%-X7R";"0402";"47pF ceramic capacitors";"";"";"";"";"CAP-15063";"";"";"";"47pF";
"C2";"1.0uF";"1.0UF-0603-16V-10%-X7R";"0603";"1µF ceramic capacitors";"";"";"";"";"CAP-13930";"";"";"";"1.0uF";
"C3";"0.1uF";"0.1UF-0603-25V-(+80/-20%)";"0603";"0.1µF ceramic capacitors";"";"";"";"";"CAP-00810";"";"";"";"0.1uF";
"C4";"1.0uF";"1.0UF-0603-16V-10%-X7R";"0603";"1µF ceramic capacitors";"";"";"";"";"CAP-13930";"";"";"";"1.0uF";
"C5";"0.1uF";"0.1UF-0603-25V-5%";"0603";"0.1µF ceramic capacitors";"";"";"";"";"CAP-08604";"";"";"";"0.1uF";
"C6";"1.0uF";"1.0UF-0603-16V-10%-X7R";"0603";"1µF ceramic capacitors";"";"";"";"";"CAP-13930";"";"";"";"1.0uF";
"C7";"0.1uF";"0.1UF-0603-25V-5%";"0603";"0.1µF ceramic capacitors";"";"";"";"";"CAP-08604";"";"";"";"0.1uF";
"C8";"4.7uF";"4.7UF-0603-35V-(20%)";"0603";"4.7µF ceramic capacitors";"";"";"";"";"CAP-14106";"";"";"";"4.7uF";
"C9";"4.7uF";"4.7UF-0603-35V-(20%)";"0603";"4.7µF ceramic capacitors";"";"";"";"";"CAP-14106";"";"";"";"4.7uF";
"C10";"10uF";"10UF-0603-6.3V-20%";"0603";"10.0µF ceramic capacitors";"";"";"";"";"CAP-11015";"";"";"";"10uF";
"C11";"0.1uF";"0.1UF-0603-25V-(+80/-20%)";"0603";"0.1µF ceramic capacitors";"";"";"";"";"CAP-00810";"";"";"";"0.1uF";
"C12";"0.1uF";"0.1UF-0603-25V-(+80/-20%)";"0603";"0.1µF ceramic capacitors";"";"";"";"";"CAP-00810";"";"";"";"0.1uF";
"C13";"0.1uF";"0.1UF-0603-25V-(+80/-20%)";"0603";"0.1µF ceramic capacitors";"";"";"";"";"CAP-00810";"";"";"";"0.1uF";
"C14";"10uF";"10UF-0603-6.3V-20%";"0603";"10.0µF ceramic capacitors";"";"";"";"";"CAP-11015";"";"";"";"10uF";
"C15";"0.1uF";"0.1UF-0603-25V-(+80/-20%)";"0603";"0.1µF ceramic capacitors";"";"";"";"";"CAP-00810";"";"";"";"0.1uF";
"C16";"0.1uF";"0.1UF-0603-25V-(+80/-20%)";"0603";"0.1µF ceramic capacitors";"";"";"";"";"CAP-00810";"";"";"";"0.1uF";
"C17";"1.0uF";"1.0UF-0603-16V-10%-X7R";"0603";"1µF ceramic capacitors";"";"";"";"";"CAP-13930";"";"";"";"1.0uF";
"C18";"1.0uF";"1.0UF-0603-16V-10%-X7R";"0603";"1µF ceramic capacitors";"";"";"";"";"CAP-13930";"";"";"";"1.0uF";
"C19";"10uF";"10UF-0603-6.3V-20%";"0603";"10.0µF ceramic capacitors";"";"";"";"";"CAP-11015";"";"";"";"10uF";
"C20";"10uF";"10UF-0603-6.3V-20%";"0603";"10.0µF ceramic capacitors";"";"";"";"";"CAP-11015";"";"";"";"10uF";
"C21";"0.1uF";"0.1UF-0603-25V-(+80/-20%)";"0603";"0.1µF ceramic capacitors";"";"";"";"";"CAP-00810";"";"";"";"0.1uF";
"C22";"0.1uF";"0.1UF-0603-25V-5%";"0603";"0.1µF ceramic capacitors";"";"";"";"";"CAP-08604";"";"";"";"0.1uF";
"C23";"0.1uF";"0.1UF-0603-25V-5%";"0603";"0.1µF ceramic capacitors";"";"";"";"";"CAP-08604";"";"";"";"0.1uF";
"C27";"0.1uF";"0.1UF-0603-25V-(+80/-20%)";"0603";"0.1µF ceramic capacitors";"";"";"";"";"CAP-00810";"";"";"";"0.1uF";
"C28";"0.1uF";"0.1UF-0603-25V-(+80/-20%)";"0603";"0.1µF ceramic capacitors";"";"";"";"";"CAP-00810";"";"";"";"0.1uF";
"C29";"0.1uF";"0.1UF-0603-25V-(+80/-20%)";"0603";"0.1µF ceramic capacitors";"";"";"";"";"CAP-00810";"";"";"";"0.1uF";
"D1";"250mA/100V";"DIODE-BAS16J";"SOD-323";"Diode";"";"";"";"";"DIO-09646";"";"";"";"250mA/100V";
"D2";"PRTR5V0U2F";"PRTR5V0U2F";"SOT886";"A small ESD protection device. Most commonly used on USB D+/D- signals to protect large, expensive, or especially sensitive USB enabled devices.";"";"";"";"";"DIO-14084";"";"";"";"";
"D3";"3A/10V/280mV";"DIODE-SCHOTTKY-BAT60A";"SOD-323";"Schottky diode";"";"";"";"";"DIO-14072";"";"";"";"3A/10V/280mV";
"D6";"PRTR5V0U2F";"PRTR5V0U2F";"SOT886";"A small ESD protection device. Most commonly used on USB D+/D- signals to protect large, expensive, or especially sensitive USB enabled devices.";"";"";"";"";"DIO-14084";"";"";"";"";
"D7";"3A/10V/280mV";"DIODE-SCHOTTKY-BAT60A";"SOD-323";"Schottky diode";"";"";"";"";"DIO-14072";"";"";"";"3A/10V/280mV";
"D9";"3A/10V/280mV";"DIODE-SCHOTTKY-BAT60A";"SOD-323";"Schottky diode";"";"";"";"";"DIO-14072";"";"";"";"3A/10V/280mV";
"D10";"PESD0402-0402";"PESD0402-0402";"0402";"ESD protection diode";"";"";"PESD0402-140CT-ND";"650-PESD0402-140";"DIO-15359";"";"";"";"";
"E1";"SMA";"ANTENNA-SMA-GROUNDEDEDGE_SMA";"SMA-EDGE";"SMA Antenna Connector w/ Ground";"";"";"";"";"CONN-08289";"";"";"";"";
"FB1";"2.66Ω";"FERRITE_BEAD-0402-2.66Ω-1GHZ";"0402-TIGHT";"Ferrite Bead (blocks, cores, rings, chokes, etc.)";"";"";"";"";"NDUC-15072";"";"";"";"2.66Ω";
"FRAME2";"FRAME-LEDGER";"FRAME-LEDGER";"CREATIVE_COMMONS";"Schematic Frame - Ledger";"";"";"";"";"";"";"";"";"";
"FRAME3";"FRAME-LEDGERNO_FOOTPRINT";"FRAME-LEDGERNO_FOOTPRINT";"DUMMY";"Schematic Frame - Ledger";"N. Seidle";"";"";"";"";"v10";"";"";"";
"J1";"";"CONN_021X02_NO_SILK";"1X02_NO_SILK";"Multi connection point. Often used as Generic Header-pin footprint for 0.1 inch spaced/style header connections";"";"";"";"";"";"";"";"";"";
"J2";"";"CONN_04JST-SMD-LOCKING";"JST-4-SMD-1.25MM-LOCKING";"Multi connection point. Often used as Generic Header-pin footprint for 0.1 inch spaced/style header connections";"";"";"";"";"CONN-15303";"";"";"";"";
"J3";"USB Female Type C Connector";"USB_C_4-LAYER_PADS";"USB-C-16P_4LAYER-PADS";"USB Type C 16Pin Connector";"";"";"";"";"CONN-14122";"";"";"";"";
"J4";"External";"I2C_STANDARDQWIIC";"JST04_1MM_RA";"SparkFun I2C Standard Pinout Header";"";"";"";"";"CONN-13694";"";"";"";"Qwiic Right Angle";
"J5";"USB Female Type C Connector";"USB_C_4-LAYER_PADS";"USB-C-16P_4LAYER-PADS";"USB Type C 16Pin Connector";"";"";"";"";"CONN-14122";"";"";"";"";
"J6";"";"CONN_05NO_SILK";"1X05_NO_SILK";"Multi connection point. Often used as Generic Header-pin footprint for 0.1 inch spaced/style header connections";"";"";"";"";"";"";"";"";"";
"J7";"";"CONN_041X04_NO_SILK_NO_POP";"1X04_NO_SILK";"Multi connection point. Often used as Generic Header-pin footprint for 0.1 inch spaced/style header connections";"";"";"";"";"";"";"";"";"";
"J8";"";"JST_2MM_MALE";"JST-2-SMD";"JST 2MM MALE RA CONNECTOR";"";"";"";"";"CONN-11443";"";"PRT-08612";"";"";
"J9";"";"CONN_04JST-SMD-LOCKING";"JST-4-SMD-1.25MM-LOCKING";"Multi connection point. Often used as Generic Header-pin footprint for 0.1 inch spaced/style header connections";"";"";"";"";"CONN-15303";"";"";"";"";
"J10";"";"CONN_021X02_NO_SILK";"1X02_NO_SILK";"Multi connection point. Often used as Generic Header-pin footprint for 0.1 inch spaced/style header connections";"";"";"";"";"";"";"";"";"";
"J11";"";"CONN_041X04_NO_SILK_NO_POP";"1X04_NO_SILK";"Multi connection point. Often used as Generic Header-pin footprint for 0.1 inch spaced/style header connections";"";"";"";"";"";"";"";"";"";
"J12";"";"CONN_041X04_NO_SILK_NO_POP";"1X04_NO_SILK";"Multi connection point. Often used as Generic Header-pin footprint for 0.1 inch spaced/style header connections";"";"";"";"";"";"";"";"";"";
"J13";"Internal";"I2C_STANDARDQWIIC";"JST04_1MM_RA";"SparkFun I2C Standard Pinout Header";"";"";"";"";"CONN-13694";"";"";"";"Qwiic Right Angle";
"J14";"";"CONN_021X02_NO_SILK";"1X02_NO_SILK";"Multi connection point. Often used as Generic Header-pin footprint for 0.1 inch spaced/style header connections";"";"";"";"";"";"";"";"";"";
"J15";"";"CONN_021X02_NO_SILK";"1X02_NO_SILK";"Multi connection point. Often used as Generic Header-pin footprint for 0.1 inch spaced/style header connections";"";"";"";"";"";"";"";"";"";
"J16";"MICRO-SD-PUSH-PUSH-EXT-PIN";"MICRO-SD-PUSH-PUSH-EXT-PIN";"MICROSD-EXTERNALPIN";"microSD Socket for Transflash";"";"";"";"";"CONN-16110";"";"";"";"";
"J17";"Qwiic Right Angle";"I2C_STANDARD_NO_SILK";"1X04_NO_SILK";"SparkFun I2C Standard Pinout Header";"";"";"";"";"";"";"";"";"";
"J18";"";"CONN_01PTH_NO_SILK_YES_STOP";"1X01_NO_SILK";"Single connection point. Often used as Generic Header-pin footprint for 0.1 inch spaced/style header connections";"";"";"";"";"";"";"";"";"";
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

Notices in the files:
parts and their libraries:
RELEASED UNDER THE CREATIVE COMMONS ATTRIBUTION SHARE-ALIKE 4.0 LICENSE
HTTPS://CREATIVECOMMONS.ORG/LICENSES/BY-SA/4.0
